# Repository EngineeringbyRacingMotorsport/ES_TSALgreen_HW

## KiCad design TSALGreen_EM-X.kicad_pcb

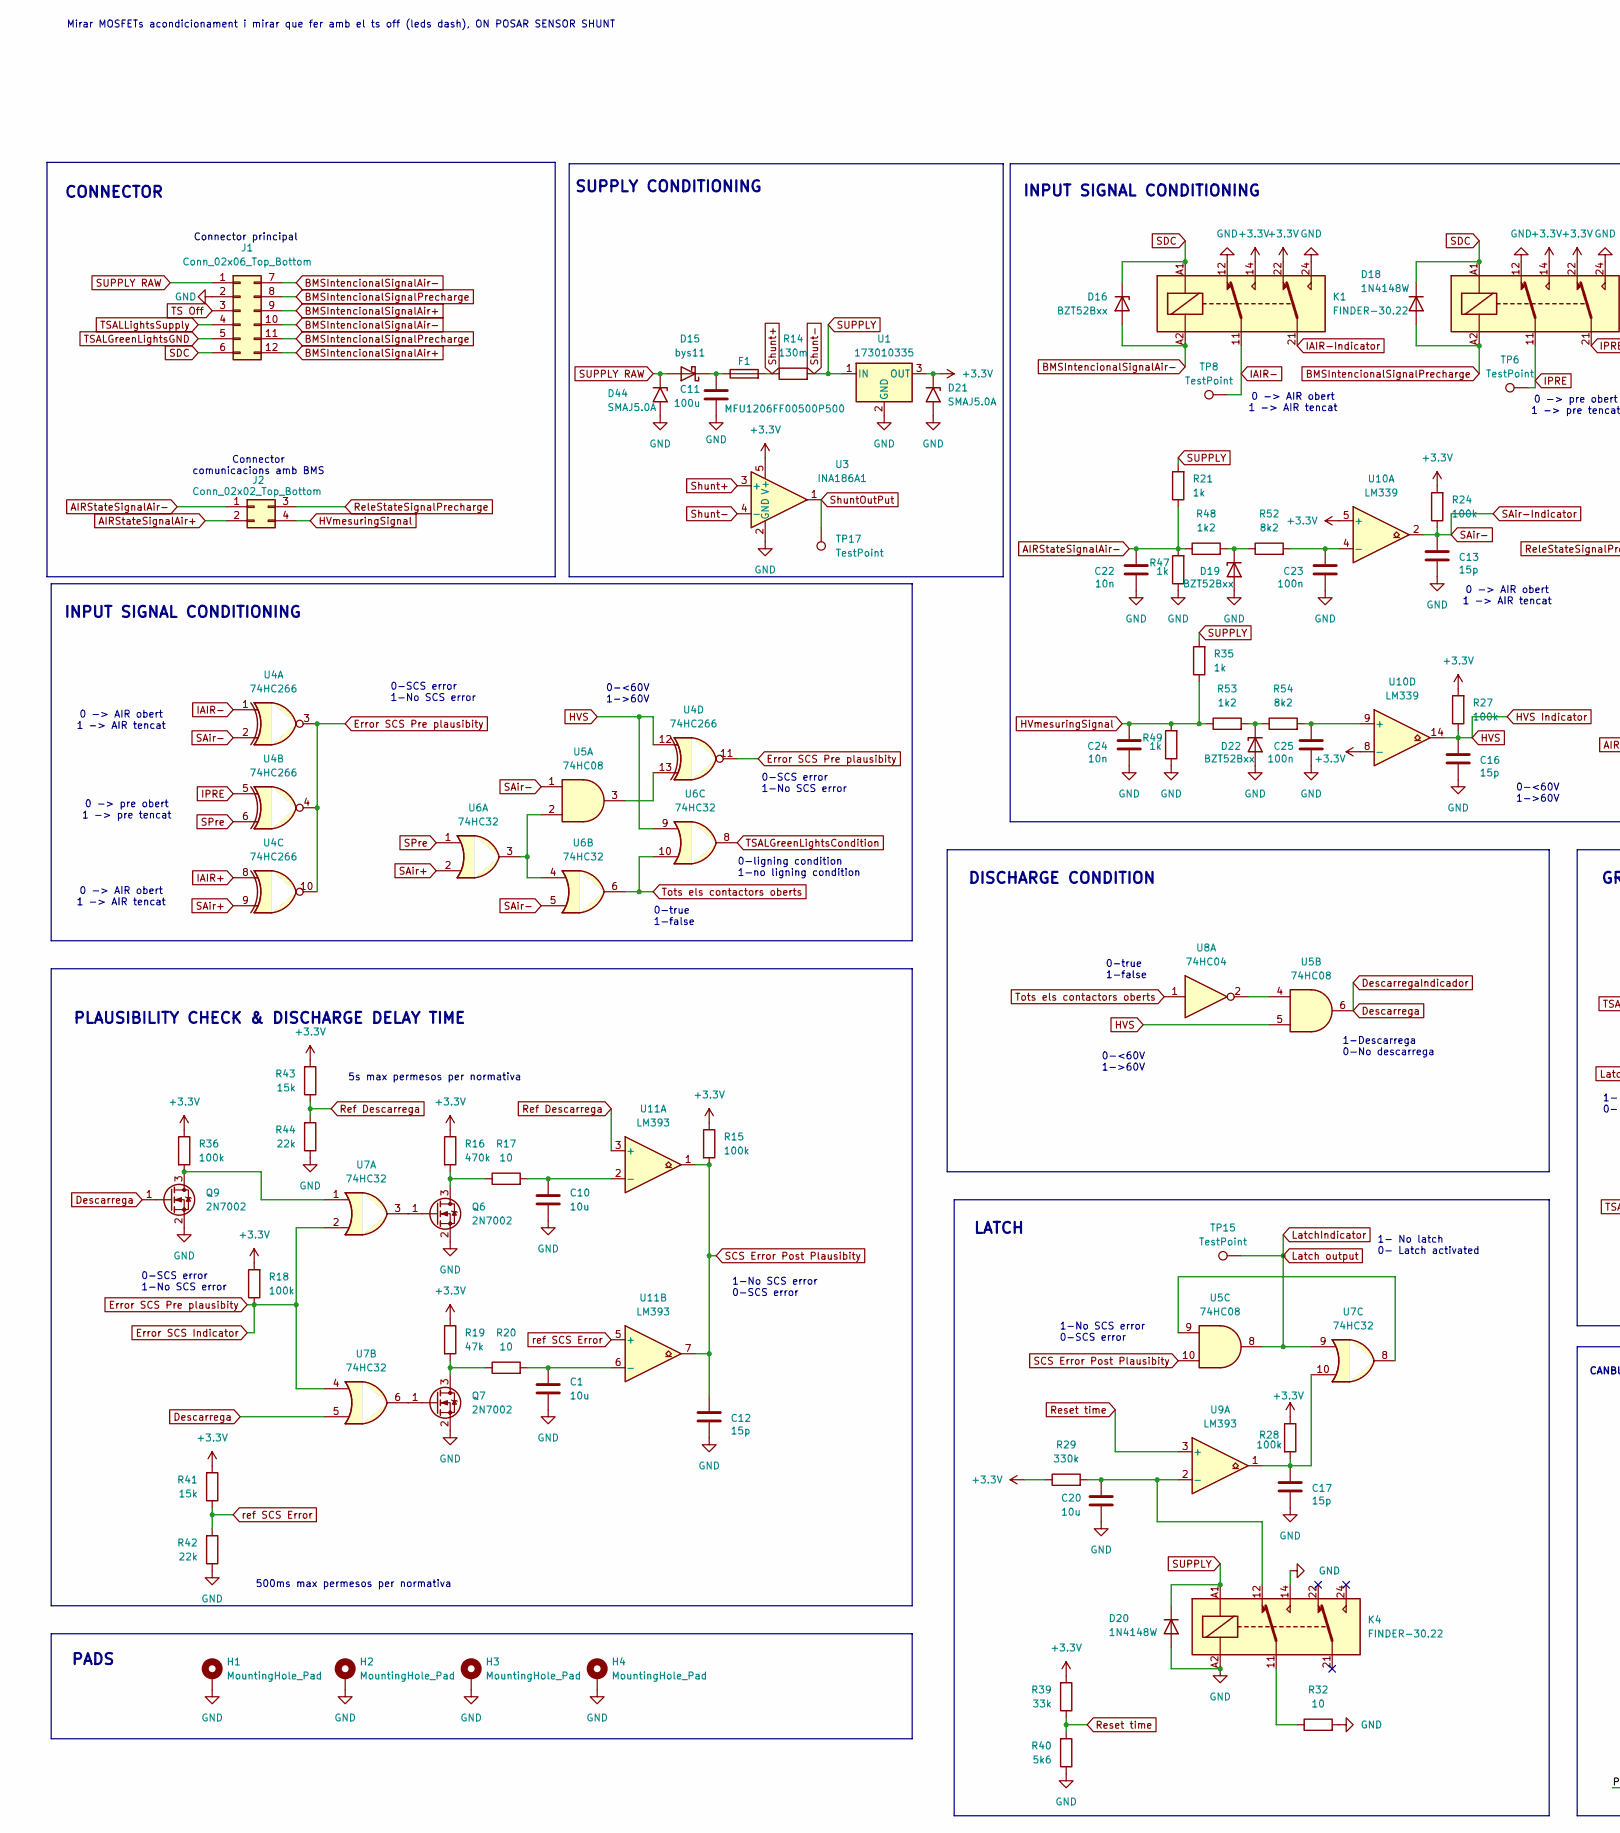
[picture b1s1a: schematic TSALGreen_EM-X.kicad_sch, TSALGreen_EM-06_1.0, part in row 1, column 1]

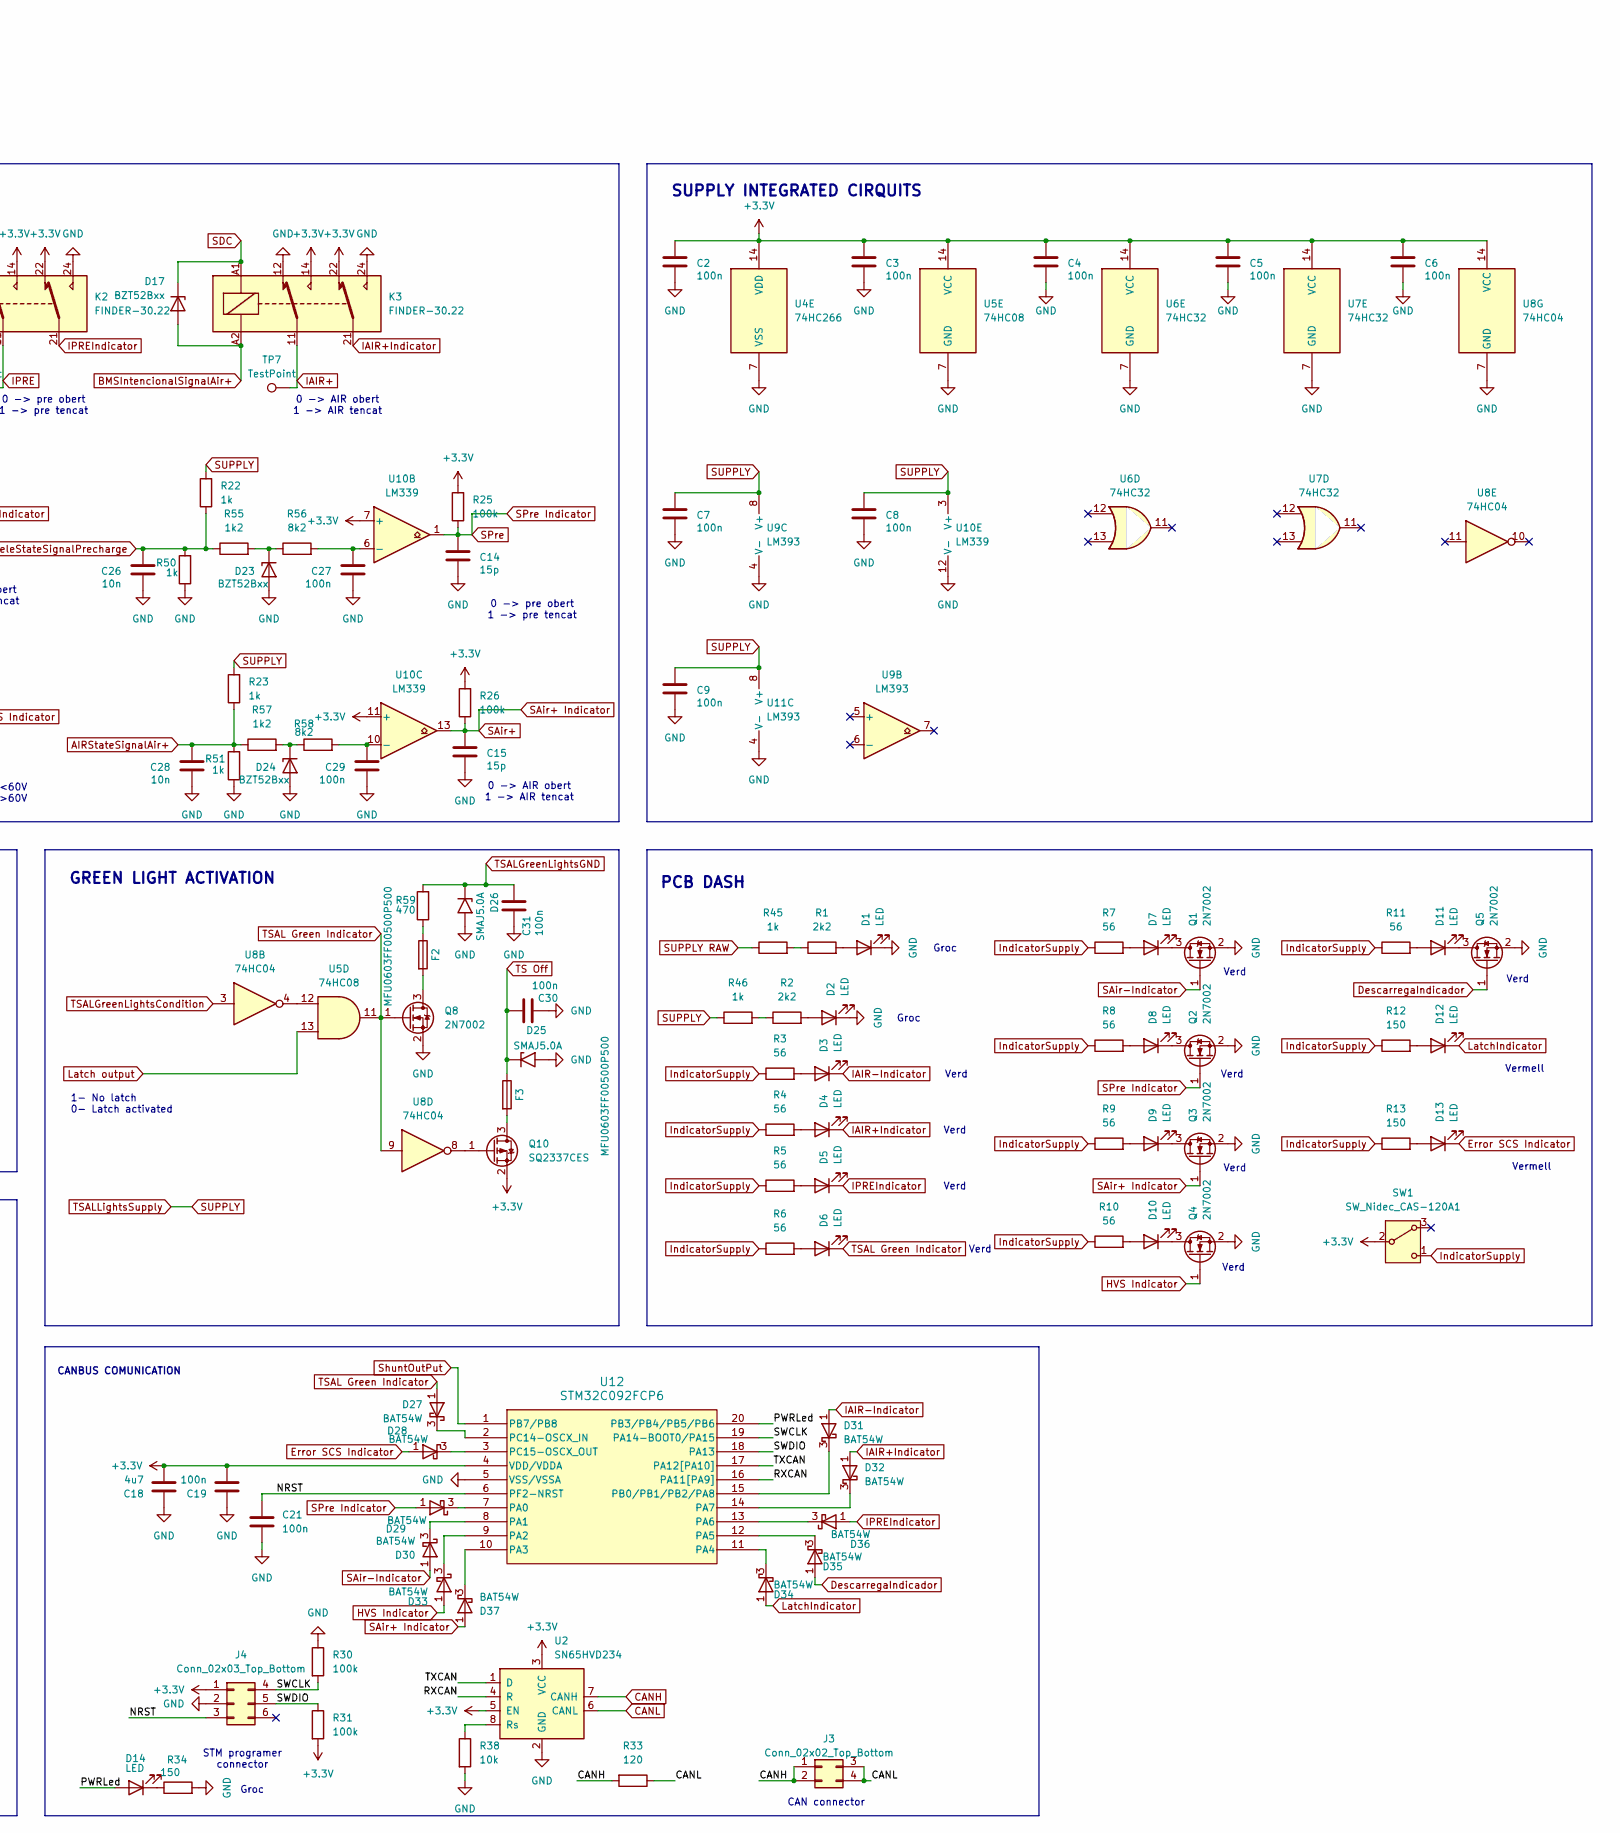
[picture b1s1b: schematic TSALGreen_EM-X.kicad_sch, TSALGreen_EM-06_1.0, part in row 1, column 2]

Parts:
C1, C10, C20: 10u; C_0603_1608Metric
C2, C3, C4, C5, C6, C7, C8, C9, C19, C21, C23, C25, C27, C29, C30, C31: 100n; C_0603_1608Metric
C11: 100u; CP_Elec_10x10
C12, C13, C14, C15, C16, C17: 15p; C_0603_1608Metric
C18: 4u7; C_0603_1608Metric
C22, C24, C26, C28: 10n; C_0603_1608Metric
D1, D2, D3, D4, D5, D6, D7, D8, D9, D10, D11, D12, D13, D14: LED; LED_0603_1608Metric
D15: bys11; D_SMA
D16, D17, D19, D22, D23, D24: BZT52Bxx; D_SOD-123F
D18, D20: 1N4148W; D_SOD-123
D21, D25, D26, D44: SMAJ5.0A; D_SMA
D27, D28, D29, D30, D31, D32, D33, D34, D35, D36, D37: BAT54W; SOT-323_SC-70
F1: MFU1206FF00500P500; Fuse_1206_3216Metric
F2, F3: MFU0603FF00500P500; Fuse_0603_1608Metric
H1, H2, H3, H4: MountingHole_Pad; MountingHole_3.5mm_Pad_Via
J1: Conn_02x06_Top_Bottom; Molex_Nano-Fit_105314-xx12_2x06_P2.50mm_Horizontal
J2, J3: Conn_02x02_Top_Bottom; Molex_Nano-Fit_105314-xx04_2x02_P2.50mm_Horizontal
J4: Conn_02x03_Top_Bottom; Molex_Nano-Fit_105310-xx06_2x03_P2.50mm_Vertical
K1, K2, K3, K4: FINDER-30.22; Relay_DPDT_Finder_30.22
Q1, Q2, Q3, Q4, Q5, Q6, Q7, Q8, Q9: 2N7002; SOT-23
Q10: SQ2337CES; SOT-23
R1, R2: 2k2; R_1206_3216Metric
R3, R4, R5, R6, R7, R8, R9, R10, R11: 56; R_0603_1608Metric
R12, R13, R34: 150; R_0603_1608Metric
R14: 130m; R_0603_1608Metric
R15, R18, R24, R25, R26, R27, R28, R30, R31, R36: 100k; R_0603_1608Metric
R16: 470k; R_0603_1608Metric
R17, R20, R32: 10; R_0603_1608Metric
R19: 47k; R_0603_1608Metric
R21, R22, R23, R35, R47, R49, R50, R51: 1k; R_0603_1608Metric
R29: 330k; R_0603_1608Metric
R33: 120; R_0603_1608Metric
R38: 10k; R_0603_1608Metric
R39: 33k; R_0603_1608Metric
R40: 5k6; R_0603_1608Metric
R41, R43: 15k; R_0603_1608Metric
R42, R44: 22k; R_0603_1608Metric
R45, R46: 1k; R_1206_3216Metric
R48, R53, R55, R57: 1k2; R_0603_1608Metric
R52, R54, R56, R58: 8k2; R_0603_1608Metric
R59: 470; R_0603_1608Metric
SW1: SW_Nidec_CAS-120A1; Nidec_Copal_CAS-120A
TP6, TP7, TP8, TP15, TP17: TestPoint; TestPoint_Pad_D1.0mm
U1: 173010335; Converter_DCDC_RECOM_R-78E-0.5_THT
U2: SN65HVD234; SOIC-8_3.9x4.9mm_P1.27mm
U3: INA186A1; SOT-23-5
U4: 74HC266; SOIC-14_3.9x8.7mm_P1.27mm
U5: 74HC08; TSSOP-14_4.4x5mm_P0.65mm
U6, U7: 74HC32; TSSOP-14_4.4x5mm_P0.65mm
U8: 74HC04; TSSOP-14_4.4x5mm_P0.65mm
U9, U11: LM393; TSSOP-8_4.4x3mm_P0.65mm
U10: LM339; TSSOP-14_4.4x5mm_P0.65mm
U12: STM32C092FCP6; TSSOP-20_4.4x6.5mm_P0.65mm

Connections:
+3.3V: C2.1, C3.1, C4.1, C5.1, C6.1, C18.2, C19.2, D21.1 (A1), J4.1, K1.14, K1.22, K2.14, K2.22, K3.14, K3.22, Q10.2 (S), R15.1, R16.1, R18.2, R19.1, R24.2, R25.2, R26.2, R27.2, R28.1, R29.1, R31.2, R36.1, R39.2, R41.2, R43.2, SW1.2 (B), U1.3 (OUT), U2.3 (VCC), U2.5 (EN), U3.5 (V+), U4.14 (VDD), U5.14 (VCC), U6.14 (VCC), U7.14 (VCC), U8.14 (VCC), U10.5 (+), U10.7 (+), U10.8 (-), U10.11 (+), U12.4 (VDD/VDDA)
/NRST: C21.1, J4.3, U12.6 (PF2-NRST)
/PWRLed: D14.2 (A), U12.20 (PB3/PB4/PB5/PB6)
/RXCAN: U2.4 (R), U12.16 (PA11[PA9])
/SWCLK: J4.4, R30.2, U12.19 (PA14-BOOT0/PA15)
/SWDIO: J4.5, R31.1, U12.18 (PA13)
/TXCAN: U2.1 (D), U12.17 (PA12[PA10])
AIRStateSignalAir+: C28.1, J2.2, R23.1, R51.2, R57.1
AIRStateSignalAir-: C22.1, J2.1, R21.1, R47.2, R48.1
BMSIntencionalSignalAir+: D17.2 (A), J1.9, J1.12, K3.A2
BMSIntencionalSignalAir-: D16.2 (A), J1.7, J1.10, K1.A2
BMSIntencionalSignalPrecharge: D18.2 (A), J1.8, J1.11, K2.A2
CANH: J3.1, J3.2, R33.2, U2.7 (CANH)
CANL: J3.3, J3.4, R33.1, U2.6 (CANL)
Descarrega: D35.1 (A), Q5.1 (G), Q9.1 (G), U5.6, U7.5
Error SCS Indicator: D13.1 (K), D28.1 (A), R18.1, U4.3, U4.4, U4.10, U4.11, U7.2, U7.4
GND: C1.2, C2.2, C3.2, C4.2, C5.2, C6.2, C7.2, C8.2, C9.2, C10.2, C11.2, C12.2, C13.2, C14.2, C15.2, C16.2, C17.2, C18.1, C19.1, C20.2, C21.2, C22.2, C23.2, C24.2, C25.2, C26.2, C27.2, C28.2, C29.2, C30.1, C31.1, D1.1 (K), D2.1 (K), D19.2 (A), D20.2 (A), D21.2 (A2), D22.2 (A), D23.2 (A), D24.2 (A), D25.2 (A2), D26.2 (A2), D44.2 (A2), H1.1 (1_1), H2.1 (1_1), H3.1 (1_1), H4.1 (1_1), J1.2, J4.2, K1.12, K1.24, K2.12, K2.24, K3.12, K3.24, K4.14, K4.A2, Q1.2 (S), Q2.2 (S), Q3.2 (S), Q4.2 (S), Q5.2 (S), Q6.2 (S), Q7.2 (S), Q8.2 (S), Q9.2 (S), R30.1, R32.2, R34.2, R38.2, R40.1, R42.1, R44.1, R47.1, R49.1, R50.1, R51.1, U1.2 (GND), U2.2 (GND), U3.2 (GND), U4.7 (VSS), U5.7 (GND), U6.7 (GND), U7.7 (GND), U8.7 (GND), U9.4 (V-), U10.12 (V-), U11.4 (V-), U12.5 (VSS/VSSA)
HVS: C16.1, D33.1 (A), Q4.1 (G), R27.1, U4.12, U5.5, U6.9, U10.14
HVmesuringSignal: C24.1, J2.4, R35.1, R49.2, R53.1
IAIR+: K3.11, TP7.1 (1_1), U4.8
IAIR+Indicator: D4.1 (K), D32.1 (A), K3.21
IAIR-: K1.11, TP8.1 (1_1), U4.1
IAIR-Indicator: D3.1 (K), D31.1 (A), K1.21
IPRE: K2.11, TP6.1 (1_1), U4.5
IPREIndicator: D5.1 (K), D36.1 (A), K2.21
IndicatorSupply: R3.1, R4.1, R5.1, R6.1, R7.1, R8.1, R9.1, R10.1, R11.1, R12.1, R13.1, SW1.1 (C)
Latch output: D12.1 (K), D34.1 (A), TP15.1 (1_1), U5.8, U5.13, U7.9
unnamed: C17.1, R28.2, U7.10, U9.1
unnamed: D1.2 (A), R1.2
unnamed: D2.2 (A), R2.2
unnamed: D3.2 (A), R3.2
unnamed: D4.2 (A), R4.2
unnamed: D5.2 (A), R5.2
unnamed: D6.2 (A), R6.2
unnamed: D7.2 (A), R7.2
unnamed: D7.1 (K), Q1.3 (D)
unnamed: D8.2 (A), R8.2
unnamed: D8.1 (K), Q2.3 (D)
unnamed: D9.2 (A), R9.2
unnamed: D9.1 (K), Q3.3 (D)
unnamed: D10.2 (A), R10.2
unnamed: D10.1 (K), Q4.3 (D)
unnamed: D11.2 (A), R11.2
unnamed: D11.1 (K), Q5.3 (D)
unnamed: D12.2 (A), R12.2
unnamed: D13.2 (A), R13.2
unnamed: D14.1 (K), R34.1
unnamed: C11.1, D15.1 (K), F1.1
unnamed: D19.1 (K), R48.2, R52.1
unnamed: D22.1 (K), R53.2, R54.1
unnamed: D23.1 (K), R55.2, R56.1
unnamed: D24.1 (K), R57.2, R58.1
unnamed: D27.3 (K), U12.2 (PC14-OSCX_IN)
unnamed: D28.3 (K), U12.3 (PC15-OSCX_OUT)
unnamed: D29.3 (K), U12.7 (PA0)
unnamed: D30.3 (K), U12.8 (PA1)
unnamed: D31.3 (K), U12.15 (PB0/PB1/PB2/PA8)
unnamed: D32.3 (K), U12.14 (PA7)
unnamed: D33.3 (K), U12.9 (PA2)
unnamed: D34.3 (K), U12.11 (PA4)
unnamed: D35.3 (K), U12.12 (PA5)
unnamed: D36.3 (K), U12.13 (PA6)
unnamed: D37.3 (K), U12.10 (PA3)
unnamed: F2.1, R59.1
unnamed: K4.11, R32.1
unnamed: Q6.3 (D), R16.2, R17.1
unnamed: Q6.1 (G), U7.3
unnamed: Q7.3 (D), R19.2, R20.1
unnamed: Q7.1 (G), U7.6
unnamed: F2.2, Q8.3 (D)
unnamed: Q9.3 (D), R36.2, U7.1
unnamed: F3.2, Q10.3 (D)
unnamed: Q10.1 (G), U8.8
unnamed: R1.1, R45.2
unnamed: R2.1, R46.2
unnamed: R38.1, U2.8 (Rs)
unnamed: U4.13, U5.3
unnamed: U5.2, U6.3, U6.4
unnamed: U5.4, U8.2
unnamed: U5.9, U7.8
unnamed: U5.12, U8.4
unnamed: C20.1, K4.12, R29.2, U9.2 (-)
unnamed: C23.1, R52.2, U10.4 (-)
unnamed: C27.1, R56.2, U10.6 (-)
unnamed: C29.1, R58.2, U10.10 (-)
unnamed: C25.1, R54.2, U10.9 (+)
unnamed: C10.1, R17.2, U11.2 (-)
unnamed: C1.1, R20.2, U11.6 (-)
Ref Descarrega: R43.1, R44.2, U11.3 (+)
ReleStateSignalPrecharge: C26.1, J2.3, R22.1, R50.2, R55.1
Reset time: R39.1, R40.2, U9.3 (+)
SAir+: C15.1, D37.1 (A), Q3.1 (G), R26.1, U4.9, U6.2, U10.13
SAir-: C13.1, D30.1 (A), Q1.1 (G), R24.1, U4.2, U5.1, U6.5, U10.2
SCS Error Post Plausibity: C12.1, R15.2, U5.10, U11.1, U11.7
SDC: D16.1 (K), D17.1 (K), D18.1 (K), J1.6, K1.A1, K2.A1, K3.A1
SPre: C14.1, D29.1 (A), Q2.1 (G), R25.1, U4.6, U6.1, U10.1
SUPPLY: C7.1, C8.1, C9.1, D20.1 (K), J1.4, K4.A1, R14.2, R21.2, R22.2, R23.2, R35.2, R46.1, U1.1 (IN), U3.4 (-), U9.8 (V+), U10.3 (V+), U11.8 (V+)
SUPPLY RAW: D15.2 (A), D44.1 (A1), J1.1, R45.1
Shunt+: F1.2, R14.1, U3.3 (+)
ShuntOutPut: TP17.1 (1_1), U3.1, U12.1 (PB7/PB8)
TS Off: C30.2, D25.1 (A1), F3.1, J1.3
TSAL Green Indicator: D6.1 (K), D27.1 (A), Q8.1 (G), U5.11, U8.9
TSALGreenLightsCondition: U6.8, U8.3
TSALGreenLightsGND: C31.2, D26.1 (A1), J1.5, R59.2
Tots els contactors oberts: U6.6, U6.10, U8.1
ref SCS Error: R41.1, R42.2, U11.5 (+)

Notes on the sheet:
0-true 1-false
Verd
0 -> AIR obert 1 -> AIR tencat
0-ligning condition 1-no ligning condition
INPUT SIGNAL CONDITIONING
PLAUSIBILITY CHECK & DISCHARGE DELAY TIME
0-SCS error 1-No SCS error
CONNECTOR
STM programer connector
5s max permesos per normativa
0-<60V 1->60V
0 -> pre obert 1 -> pre tencat
DISCHARGE CONDITION
Vermell
GREEN LIGHT ACTIVATION
1- No latch 0- Latch activated
SUPPLY CONDITIONING
CANBUS COMUNICATION
500ms max permesos per normativa
Groc
CAN connector
Connector comunicacions amb BMS
PADS
Mirar MOSFETs acondicionament i mirar que fer amb el ts off (leds dash), ON POSAR SENSOR SHUNT
1-Descarrega 0-No descarrega
1-No SCS error 0-SCS error
PCB DASH
LATCH
SUPPLY INTEGRATED CIRQUITS
Connector principal

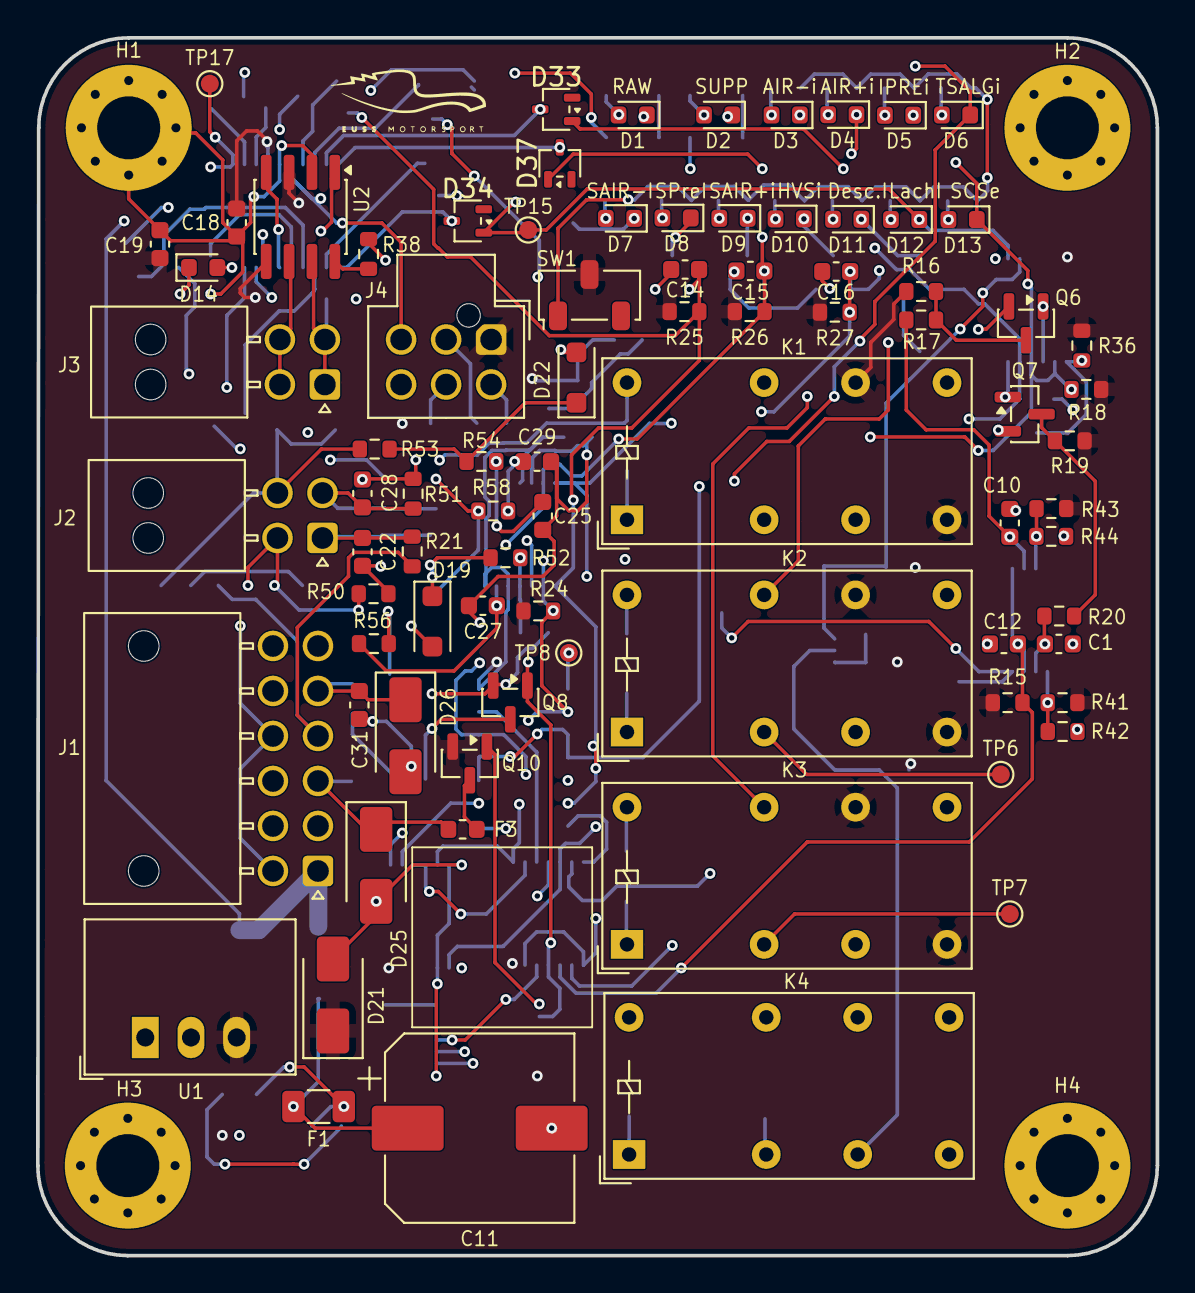
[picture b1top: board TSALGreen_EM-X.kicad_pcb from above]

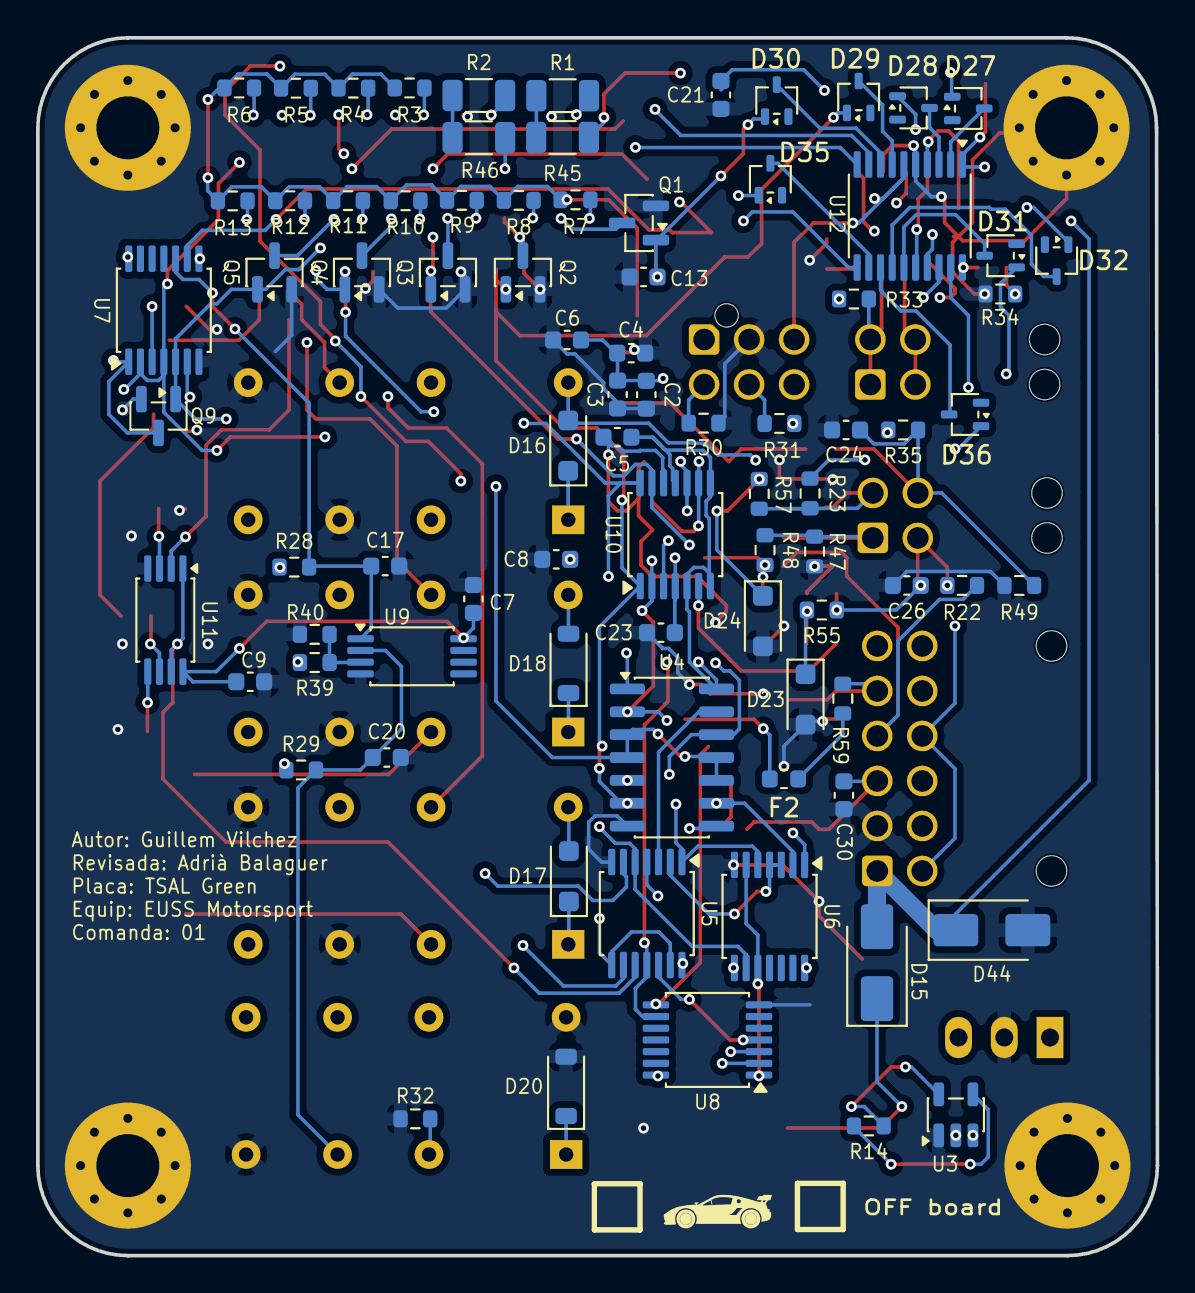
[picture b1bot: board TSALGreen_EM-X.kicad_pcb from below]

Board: 4 copper layers, 62.2 x 67.7 mm, 170 parts (83 on the bottom side), 106 nets.
